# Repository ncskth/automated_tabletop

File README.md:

### Automated Air Hockey
This repository contains all code and designs required to build and use a remote controlled air hockey table. It has been developed at the NeuroComputing Sciences (NCS) lab at KTH Royal Institute of Technology.

### Control panel
The whole table is powered with a 12V supply through the 2.1mm barrel jack. For development purposes it is also possible to power the digital control board over USB.

The fan can be toggled on and off with the button.

### Communication
The table can be controlled over both USB and Ethernet.

Attached to the USB-port there is a CH340-chip. Using this on Windows might require installing a driver. The table will show up as a virtual comport and all the settings should match the defaults. The baudrate is 1MBaud.

When ethernet is connected the table hosts a TCP server on port 1337.

Both ethernet and USB use the same communication protocol.

### Protocol
The data protocol follows a simple id-data schema. The ID is a single uint8 and it is immediately followed by N data bytes.

For a reference implementation please see [this script](control_board_fw/test.py)

#### 2 - Handshake
1. ID: 2
1. Length: 0

The control board responds with a 1.

#### 3 - Control
- ID: 3
- Length: 12
- Format
  - [x_pos: float32]
  - [y_pos: float32]
  - [velocity: float32]

Sets the target position and velocity for the handle. The units are in centimeters and centimeters per second. The floats are encoded as standard IEEE.

To run at max velocity, set the velocity to 0.

The control board responds with a 1.

#### 4 - Read position
- ID: 4
- Length: 0

Reads the current handle position. The control boards responds with 2 float32, first the X position and then the Y position for a total of 8 bytes.

#### 5 - Toggle fan
- ID: 5
- Length: 1
- Format
  - [enabled: uint8]

Enables or disables the fan. Any value other than 0 is considered to be true.

The control board responds with a 1.

### Coordinate system
The origin is in between the two servos. The Y-axis follows the board's long side and the X-axis the short side. This means that the handle can be actuated roughly in the rectangle spanned by these points `[(-10, 25), (10, 40)]`

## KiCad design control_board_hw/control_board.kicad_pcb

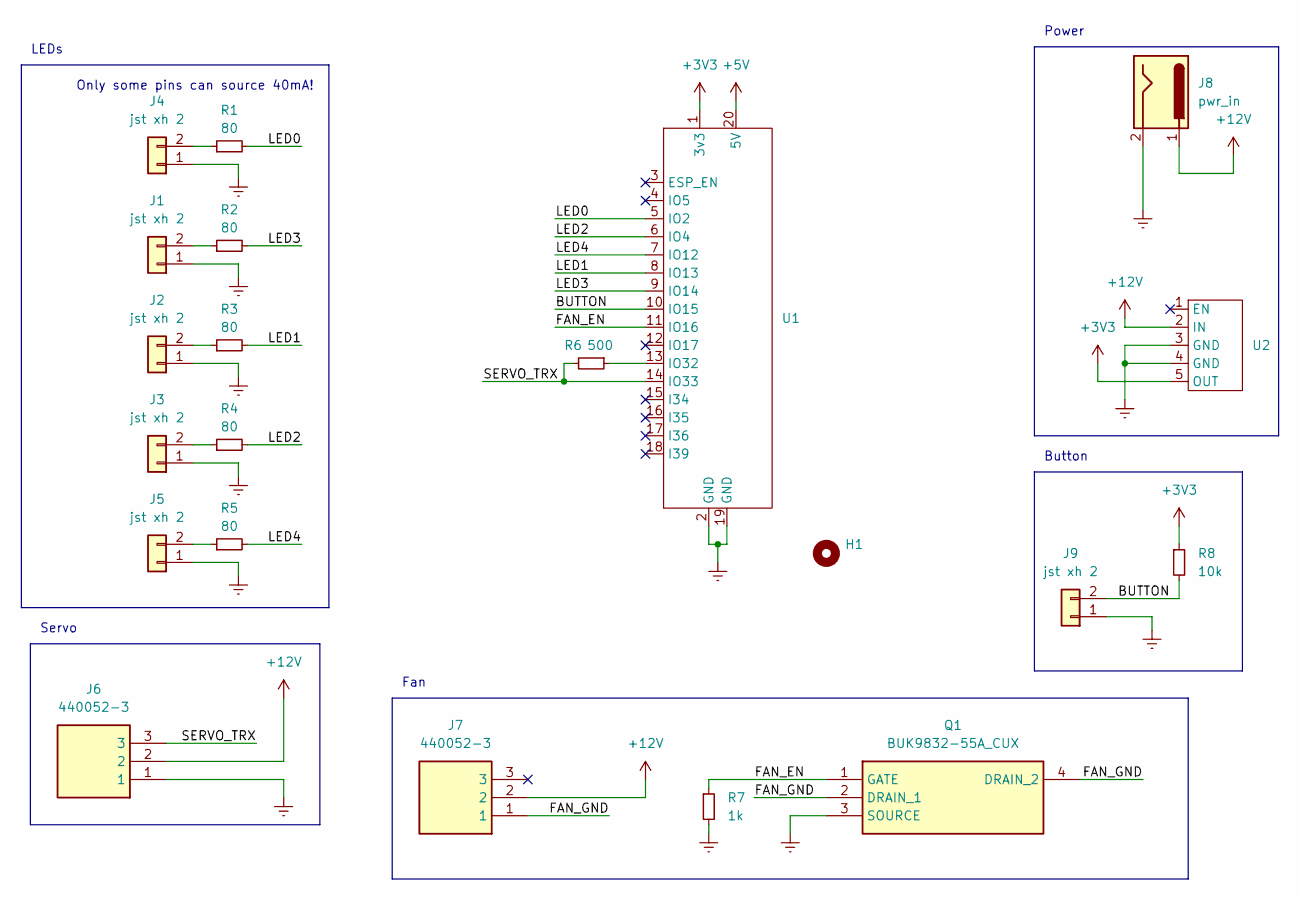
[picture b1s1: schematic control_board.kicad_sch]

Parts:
H1: MountingHole_Pad; MountingHole_3.5mm
J1, J2, J3, J4, J5, J9: jst xh 2; JST_XH_B2B-XH-A_1x02_P2.50mm_Vertical
J6, J7: 440052-3; SHDR3W64P0X250_1X3_1000X380X630P; Mouser Part Number 571-440052-3
J8: pwr_in; BarrelJack_Horizontal
Q1: BUK9832-55A_CUX; SOT230P700X180-4N; Mouser Part Number 771-BUK9832-55A/CUX
R1, R2, R3, R4, R5: 80; R_0603_1608Metric_Pad0.98x0.95mm_HandSolder
R6: 500; R_0603_1608Metric_Pad0.98x0.95mm_HandSolder
R7: 1k; R_0603_1608Metric_Pad0.98x0.95mm_HandSolder
R8: 10k; R_0603_1608Metric_Pad0.98x0.95mm_HandSolder
U1: esp32-gateway
U2: polulu-durin

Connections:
+3V3: R8.1, U1.1 (3v3), U2.5 (OUT)
+5V: U1.20 (5V)
+12V: J6.2, J7.2, J8.1, U2.2 (IN)
/BUTTON: J9.2, R8.2, U1.10 (IO15)
/FAN_EN: Q1.1 (GATE), R7.1, U1.11 (IO16)
/FAN_GND: J7.1, Q1.2 (DRAIN_1), Q1.4 (DRAIN_2)
/LED0: R1.2, U1.5 (IO2)
/LED1: R3.2, U1.8 (IO13)
/LED2: R4.2, U1.6 (IO4)
/LED3: R2.2, U1.9 (IO14)
/LED4: R5.2, U1.7 (IO12)
/SERVO_TRX: J6.3, R6.2, U1.14 (IO33)
Earth: J1.1, J2.1, J3.1, J4.1, J5.1, J6.1, J8.2, J9.1, Q1.3 (SOURCE), R7.2, U1.2 (GND), U1.19 (GND), U2.3 (GND), U2.4 (GND)
unnamed: J1.2, R2.1
unnamed: J2.2, R3.1
unnamed: J3.2, R4.1
unnamed: J4.2, R1.1
unnamed: J5.2, R5.1
unnamed: R6.1, U1.13 (IO32)

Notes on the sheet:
Only some pins can source 40mA!
Servo
Power
Fan
LEDs
Button

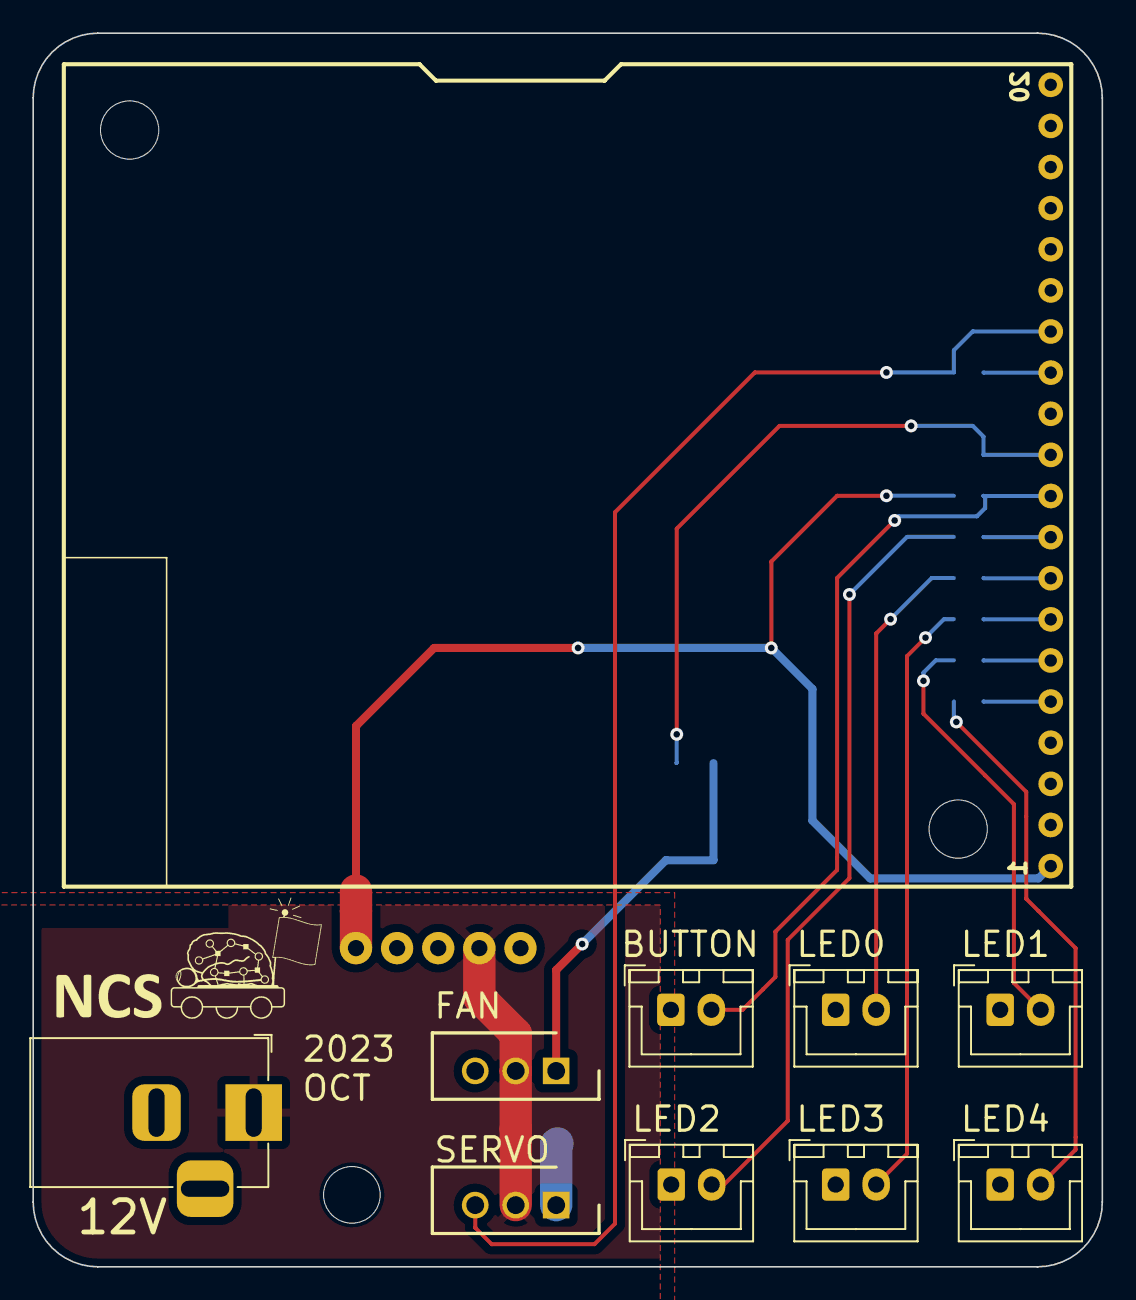
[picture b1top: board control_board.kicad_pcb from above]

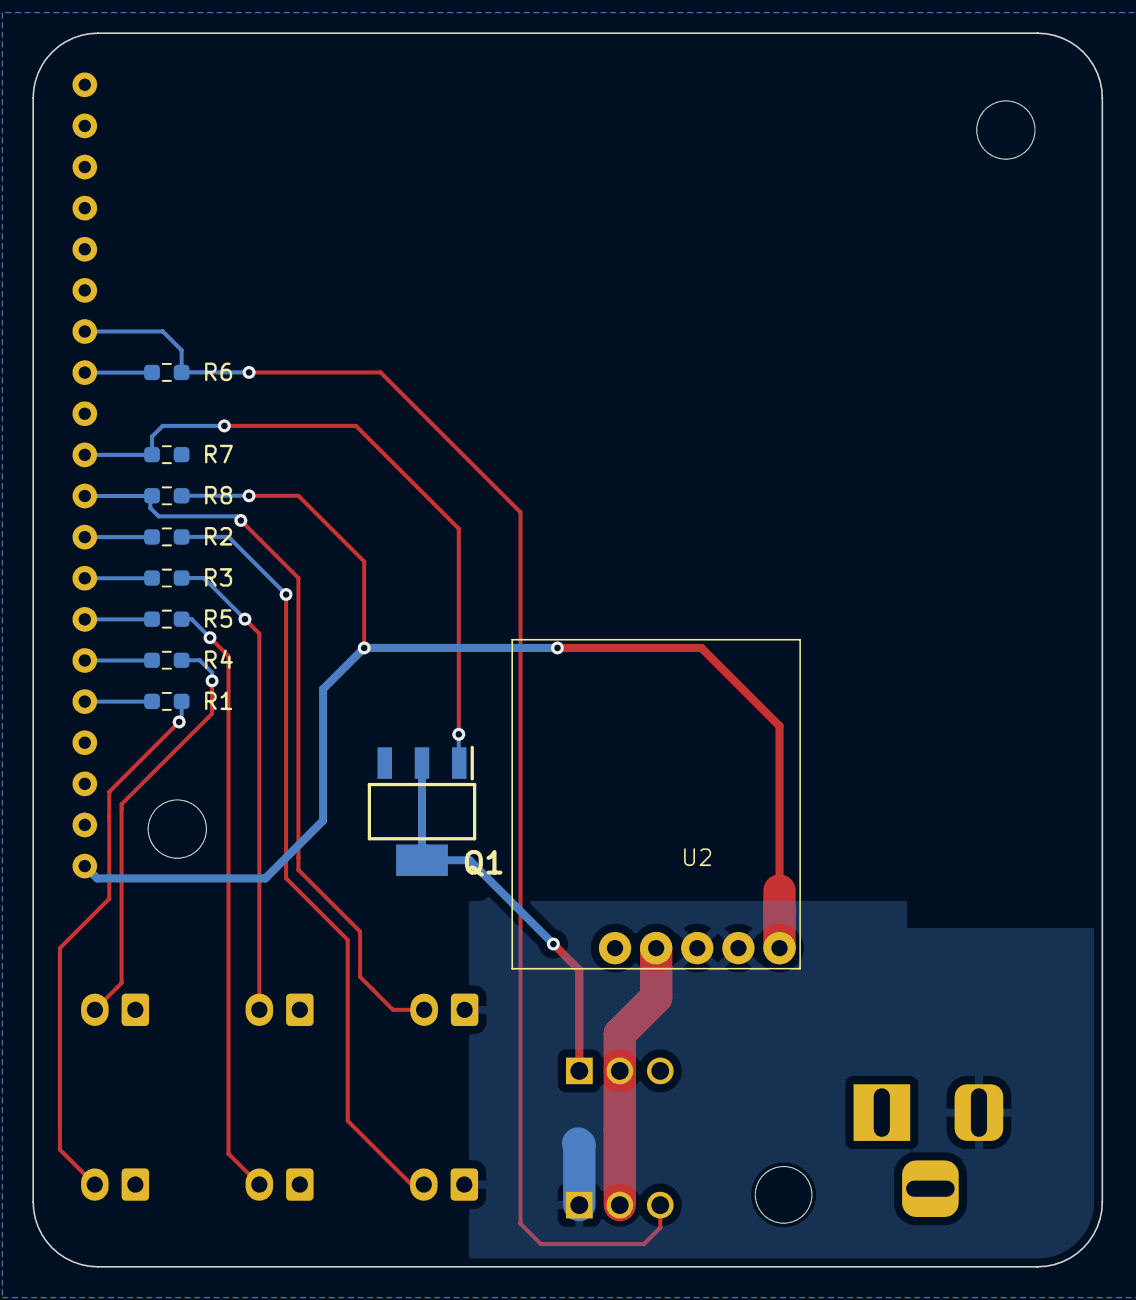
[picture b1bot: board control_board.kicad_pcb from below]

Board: 2 copper layers, 66.0 x 76.2 mm, 21 parts (10 on the bottom side), 18 nets.

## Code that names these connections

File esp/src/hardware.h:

#define PIN_LED0 13
#define PIN_LED1 4
#define PIN_LED2 14
#define PIN_LED3 -1
#define PIN_LED4 2

#define PIN_BUTTON 15
#define PIN_FAN 16
#define PIN_SERVO_RX 33
#define PIN_SERVO_TX 32
#define NUM_UART_SERVO UART_NUM_1
#define BAUD_UARD_SERVO 1000000

#define NUM_UART_CONSOLE UART_NUM_0
#define BAUD_UARD_CONSOLE 1000000

#define PI 3.1415

#define R1 23
#define R2 23
#define R3 23
#define R4 23
#define R5 10

#define LEFT_ID 1
#define RIGHT_ID 2

#define BOARD_LEFT_LIM -11
#define BOARD_RIGHT_LIM 11
#define BOARD_BOT_LIM 23
#define BOARD_TOP_LIM 44

// #define LOGGING_ENABLED

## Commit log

2023-07-28 add readme
2023-09-13 fix default motor
2023-09-13 update requirements
2023-10-24 control board v1
2023-10-25 finish control board
2024-03-05 fix velocity and position read back
2024-05-22 fix: change monitor speed to 115200
2024-05-22 feat: confirm that both servos can be position controlled and the fan control works
2024-06-17 add lots of stuff
2024-06-19 fix LED
2024-06-19 restructure
2024-06-19 remove old scripts
2024-07-02 better README
2024-07-02 even better README
